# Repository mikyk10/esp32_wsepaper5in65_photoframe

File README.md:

ESP32_WSEPaper-5in65_PhotoFrame
====

A DIY battery powered digital photo frame with color e-Paper module that periodically updates its content via Wi-Fi.

### Features

- Color ePaper
- WiFi connectivity
- Battery Powered (Optional)

## Repository Contents

This project consists of following 3 parts:

- Helper Web API (HWA)
- Firmware for [MCU](https://www.waveshare.com/e-paper-esp32-driver-board.htm)
- Battery Unit for MCU

### Helper Web API (HWA)

Randomly picks an image and transforms it into vendor specific binary data after image pre-processing. This can match up image orientation, aspect ratio, dimension, gamma, color..etc with the ePaper's hardware specification.

The vendor specific encoding for the ePaper is described here:
https://www.waveshare.com/wiki/5.65inch_e-Paper_Module_(F)_Manual#Picture_Production

### Firmware for MCU

Core software to display an image on the ePaper. It transfers encoded data to the ePaper after getting data via WiFi. It then goes into deep-sleep for certain period of time.
In order to flash the MCU, you should edit `config.h` which describes Wi-Fi credentials and the URL of HWA.

Currently it does not have a fancy Web User-Interface to manage any configuration; including WiFi SSID, password and HWA URL are statically compiled into the firmware. Everytime you change the configuration, flash the MCU. 

TLS handshake is disabled by default as it drain the battery a little more. To protect your privacy, you should place the HWA and MCU on the same private network so that your pictures will never go through internet unencrypted.

### Battery Unit for MCU

Battery power unit for MCU. It has battery charging, protection, voltage regulation circuit for a 18650 Li-Po battery cell.

PCB design is available at oshwlab.com. 
https://oshwlab.com/mikyk10/buep-esp32-db

## How to Build

### BOM

| Name                                                                                                                             | Qty | Note                                                                                                                                                                                        |
|----------------------------------------------------------------------------------------------------------------------------------|-----|---------------------------------------------------------------------------------------------------------------------------------------------------------------------------------------------|
| [Waveshare Universal e-Paper Raw Panel Driver Board](https://www.waveshare.com/e-paper-esp32-driver-board.htm)                   | 1   | The MCU for this project. You can power the MCU by plugging micro-USB instead of the Battery Unit.
                                                                                                                                                                 |
| [Waveshare 5.65inch E-Paper E-Ink Raw Display, without PCB](https://www.waveshare.com/product/displays/5.65inch-e-paper-f.htm)   | 1   | 7-Color ePaper Display module, 600×448 resolution.                                                                                                                                          |
| [Battery Unit PCB](https://u.easyeda.com/account/user/projects/index/detail?project=549b435850194f8fa61f18e4934bcfd8&folder=all) | 1   |                                                                                                                                                                                             |
| 18650 battery cell                                                                                                               | 1   | Care for the dimension. Please note some 18650 battery cell won't fit in battery holder as they have in-built protection circuit, lengthen tottal length. To avoid such case, use an unprotected cell.                                                                                                                     |
| Local network Web server                                                                                                         | 1   | I use a Raspberry pi 4B running Web server.                                                                                                                                 |
| Photo frame                                                                                                                      | 1   | Where your ePaper and stuffs go into. Get your favorite one at a hardware store. If you want to hang it on walls, you would need extra consideration for it. This repository won't cover on this.                               |
| Front panel                                                                                                                      | 1   | 2mm thick acrylic sheet with a rectangular opening for the ePaper. There are many online factory for acrylic sheet you can order. The opening dimension is equal to that of E-Paper. |
 
### Tools 

You need basic electronics toolsets.

### Build TIPS

The MCU has a red power status LED which constantly eats some current, shortens the battery life. It's directly connected to VCC so it must be physically removed if want to disable it. You can break off the LED using a plier. Be sure not to damage any other component.

## Contribution

Contribution is always welcome. You may fork this repository, change whatever you want and send me a PR.

## TODOs

- Orientation sensing / change
- Better documentation

## Disclaimer

This project is a currently PoC project, not production ready. Some artifacts are crude and a lot of work still should be done. Thus use of this is at your own risk. 
Li-Po battery cell which must be properly handled or it may explode, cause serious damages to you. 
I provide those information as reference for building a designing PCB, program code under GPLv3 license. Using them in your project may require some research of one's own, potentially fixing any issues or design flaws if they exist.

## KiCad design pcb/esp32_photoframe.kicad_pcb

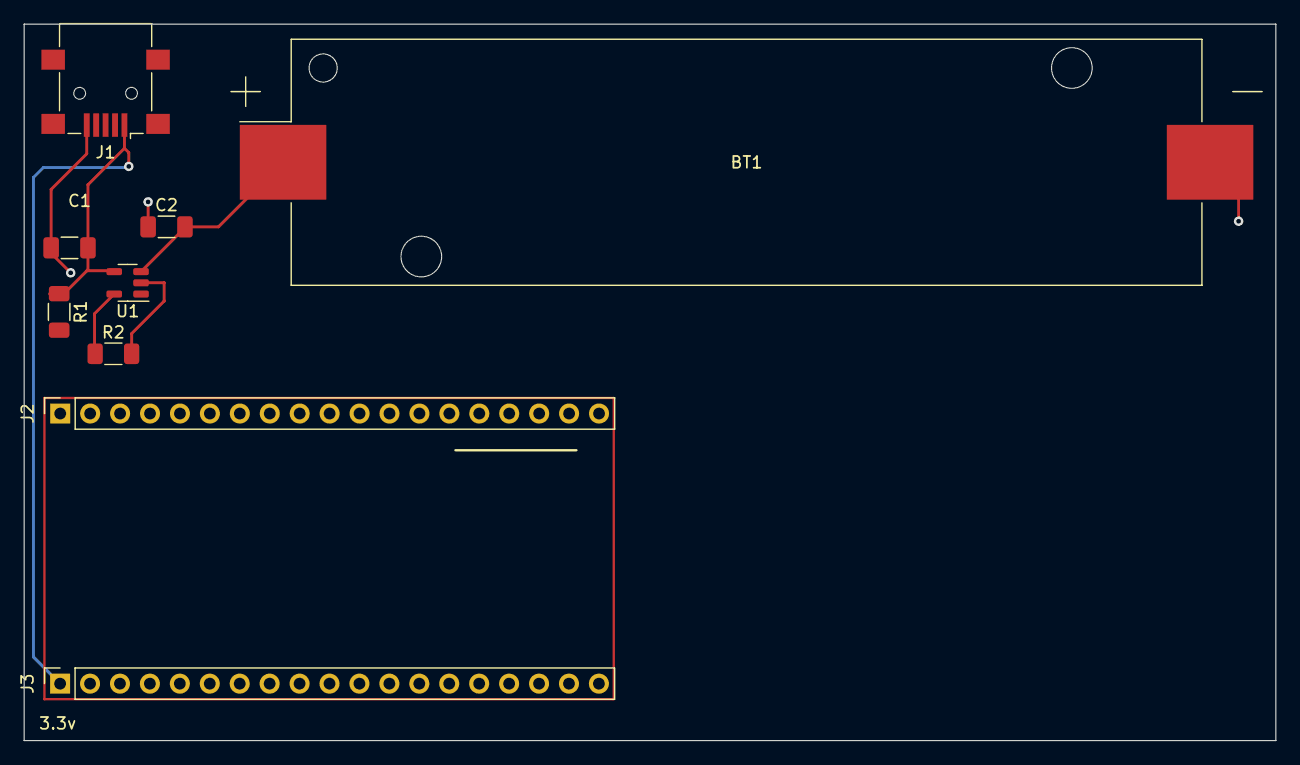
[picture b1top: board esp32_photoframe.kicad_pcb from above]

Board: 2 copper layers, 106.2 x 60.8 mm, 9 parts (0 on the bottom side), 5 nets.

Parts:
BT1: Battery_Cell; BatteryHolder_Keystone_1042_1x18650
C1, C2: C; C_1206_3216Metric_Pad1.33x1.80mm_HandSolder
J1: USB_B_Mini; USB_Mini-B_Lumberg_2486_01_Horizontal
J2, J3: Conn_01x19_Female; PinSocket_1x19_P2.54mm_Vertical
R1, R2: R; R_1206_3216Metric_Pad1.30x1.75mm_HandSolder
U1: MCP73832-5-OT; SOT-23-5

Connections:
ESP3.3V: C1.2, J1.1 (VBUS), J3.1, R1.1, U1.4 (VDD)
GND: C1.1, C2.1, J1.5 (GND), J2.1, J2.7, J3.14, J3.18
unnamed: BT1.1 (+), C2.2, U1.3 (VBAT)
unnamed: R2.1, U1.5 (PROG)
unnamed: R2.2, U1.2 (VSS)

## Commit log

2022-11-14 working progress
2022-12-07 clear the display before refresh content
